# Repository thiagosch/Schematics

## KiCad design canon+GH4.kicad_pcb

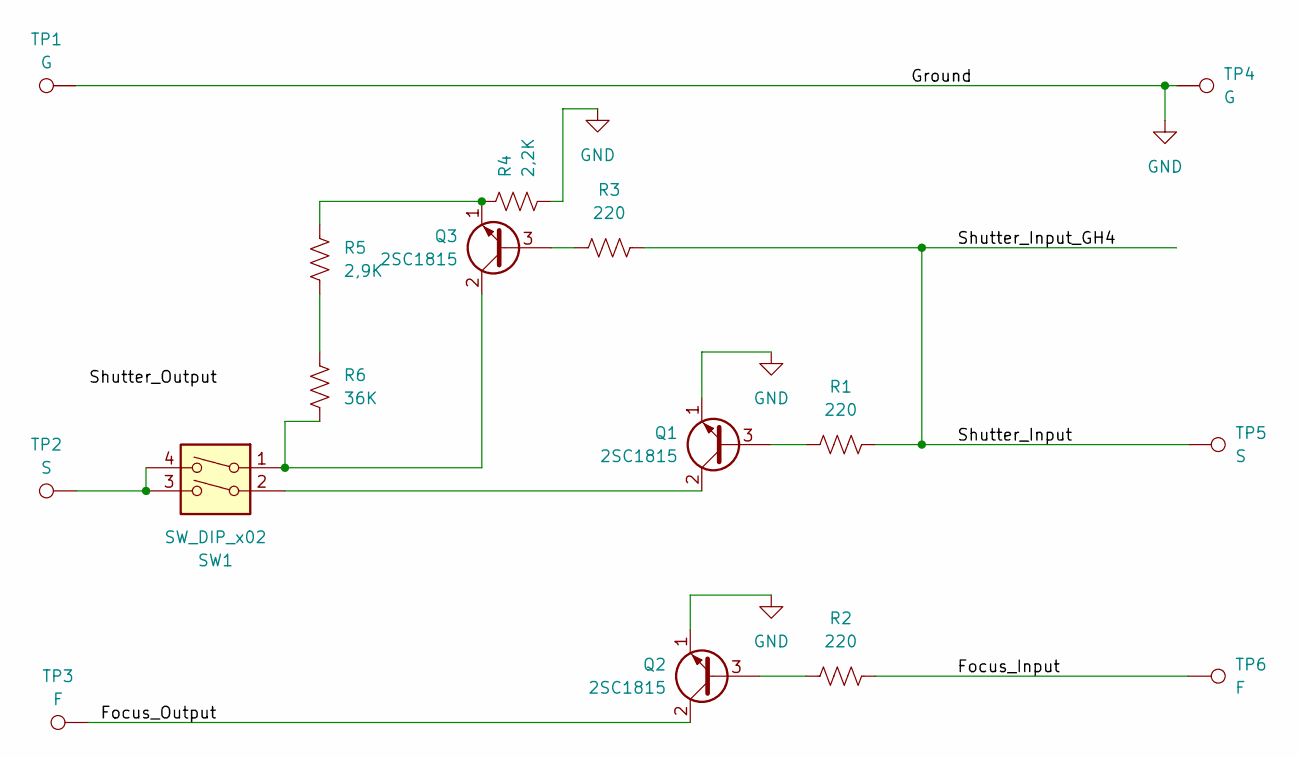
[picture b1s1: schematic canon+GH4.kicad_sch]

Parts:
Q1, Q2, Q3: 2SC1815; TO-92_Inline
R1, R2, R3: 220; R_Axial_DIN0204_L3.6mm_D1.6mm_P7.62mm_Horizontal
R4: 2,2K; R_Axial_DIN0204_L3.6mm_D1.6mm_P7.62mm_Horizontal
R5: 2,9K; R_Axial_DIN0204_L3.6mm_D1.6mm_P7.62mm_Horizontal
R6: 36K; R_Axial_DIN0204_L3.6mm_D1.6mm_P7.62mm_Horizontal
SW1: SW_DIP_x02; SW_DIP_SPSTx02_Slide_9.78x7.26mm_W7.62mm_P2.54mm
TP1, TP4: G; TestPoint_THTPad_2.0x2.0mm_Drill1.0mm
TP2, TP5: S; TestPoint_THTPad_2.0x2.0mm_Drill1.0mm
TP3, TP6: F; TestPoint_THTPad_2.0x2.0mm_Drill1.0mm

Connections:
/Focus_Input: R2.1, TP6.1
/Focus_Output: Q2.2 (C), TP3.1
/Shutter_Input: R1.1, R3.1, TP5.1
GND: Q1.1 (E), Q2.1 (E), R4.2, TP1.1, TP4.1
unnamed: Q1.3 (B), R1.2
unnamed: Q1.2 (C), SW1.2
unnamed: Q2.3 (B), R2.2
unnamed: Q3.3 (B), R3.2
unnamed: Q3.2 (C), R6.2, SW1.1
unnamed: Q3.1 (E), R4.1, R5.1
unnamed: R5.2, R6.1
unnamed: SW1.3, SW1.4, TP2.1

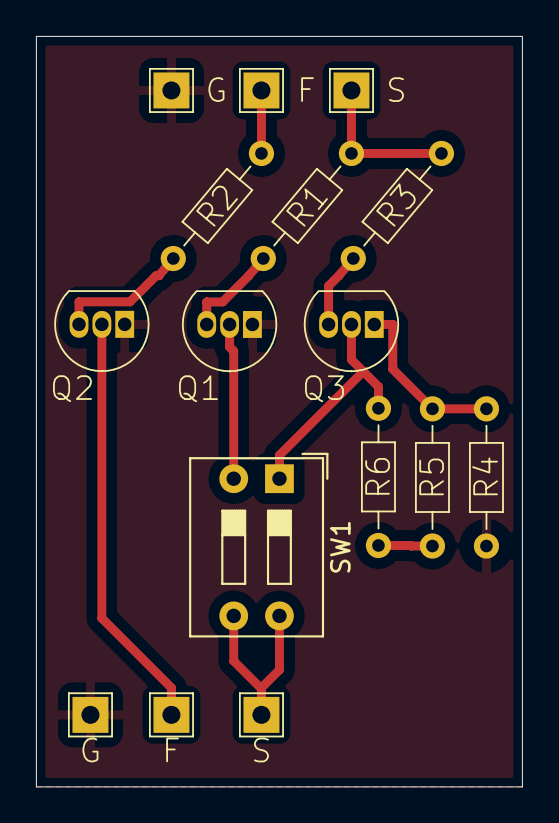
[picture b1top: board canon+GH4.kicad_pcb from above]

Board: 2 copper layers, 27.0 x 41.7 mm, 16 parts (0 on the bottom side), 12 nets.
